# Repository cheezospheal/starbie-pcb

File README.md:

# Starbie
A custom-designed PCB for a portable, interactive pet keychain that reacts to different user actions and the environment.

I initially made it only because it was the beginner project for Half Life, but I've also always been a fan of these kinds of toys. It's not only relatively easy to make, but also teaches most of the fundamentals of PCB building, such as footprints, Silkscreen, and basic Arduino code. I'm more of a creative than technical person, but I felt that this was the perfect beginner project that enhanced both. I was already interested in exploring electronics, and, using some of my own skills and interests, I think my Starbie turned out great! :)

## Summary
The PCB was designed with **KiCad** and the code was made with **Arduino**. To open the PCB yourself, install both KiCad and Arduino, then import the respective files (see below).

|File|What's Inside?|
|---|---|
|starbie_pcb.kicad_pcb|contains the PCB layout, including the routing, footprints, and edge cuts
|starbie_pcb.kicad_pro|contains the project settings and configuration
|starbie_pcb.kicad_sch|contains the schematic and connections
|Starbie.ino|contains the code used to run the micrcontroller
|starbie_pcb_gerbers.zip|contains several gerber files
|bom.csv|bill of materials

## Features
* An OLED screen that displays a small Jolteon that you can interact with
* Pet actions, including sleeping, playing, petting, and jumping
* Button controls that allow the user to trigger animations
* Custom PCB shape of a star
* Customizable interactions in the Arduino code

## Schematic
To see the schematic, open up the kicad_sch file. In the schematic, there'll be some main parts:
* XIAO-ESP32-C3-SMD: The microcontroller of the project, interpreting and executing the code
* DHT11: A sensor for temperature and humidity for interactions with the pet
* R1 10k: A 10k Ohm resistor for the DHT11
* Conn_01x08_Pin and Conn_01x04_Pin: A connector pin that links each pin to its matching circuit trace
* SW_Push: A switch/button that will control actions for the pet

The way they are connected is either through wires or through net labels (which connect parts without having to draw long wires). 

## Routing & PCB Customization
After that, take a look at the routing by opening up the kicad_pcb file.

The red lines represent the copper traces on the front of the board, while the blue lines represent the copper traces on the black of the board. These copper lines allow the microcontroller to transmit and receive data to interpret, which will then be used for the pet. Furthermore, the red overlay on top of the PCB is the GND pour. Another thing you'll notice is the customization of the PCB, including the text, images, and shape of the PCB. The shape was made using the Edge Cuts layer. To edit it, draw your own lines or move the existing vertices. Just note that you'll have to edit the GND pour as well and refill it by pressing B. I also added an extra switch, which you can see in the bottom right corner of the star. To add images, use the image converter to turn the image into a bitmap, then into a footprint, and add it on as a footprint by pressing A. KiCad has a built-in text function, so you can use that as well. Also, make sure to put the layer for both images and text as F.Silkscreen!

For my images, I uploaded a sprite of Jolteon, an apple core, and some sparkles using the method above. Just make sure that, if you are using a sprite for a game, find a scaled-up version rather than the original sprites. I also added a keychain hole as a mounting hole. KiCad will scale-up the sprite into a blurry mess that looks nothing like the original sprite. I used Wingdings for my font because it looks more interesting than just a basic readable font. 

KiCad also has a 3D viewer so you can see what your PCB will probably eventually look like!

## Firmware Customization
After making the PCB, move on to the firmware in Arduino. The code was very easy to customize, so here's the things I did to change it up and make it my own. (to change it yourself, find the specific functions)

The pet comes with basic hearts, so I decided to replace it with a lightning bolt instead. I first drew it in Piskel (or use whatever sprite art app you have), and then just wrote the code to draw it by hand. The drawPixel function works as if you were drawing pixels relative to a certain point. So, if you wanted to draw a pixel 1 pixel left of the "anchor point", you would use x - 1. 

I also used the same logic to write some code for the sparkle trail, which I just replaced with a slightly bigger sparkle that I liked better.

The biggest part was designing the pet sprite, which I have as a Jolteon. Simply draw your creature in a 32x32 size, and upload it to an image2cpp converter. I find it best to draw your own sprite. Though Jolteon already exists and there are sprites of it, it's way more personal making your own! 

the sprite I made -> 

I also made the third switch that I added have a function by making it do the ATTACK animation when pressed.

## Bill of Materials
After completely designing the PCB and finishing your code, start planning for when you actually build your PCB by ordering the parts! I created a Bill of Materials (BOM), which lists the specific names, quantities, and prices for the parts of the PCB. Use the collection of gerber files, starbiepcb_gerbers.zip, when manufacturing the PCB. The BOM is both below and in bom.csv.

Part|Quantity|Price (USD)|Vendor|Link
|---|---|---|---|---|
XIAO ESP32C3|1|$10.11|Amazon|https://www.amazon.ca/MiiElAOD-High-Performance-Cost-Effective-1PCS-Kit/dp/B0GDG7YRGW/ref=asc_df_B0GDG7YRGW?mcid=c3c8863449923deb82a1a4779cbbab0e&tag=googleshopc0c-20&linkCode=df0&hvadid=803091086323&hvpos=&hvnetw=g&hvrand=8414720962410478217&hvpone=&hvptwo=&hvqmt=&hvdev=c&hvdvcmdl=&hvlocint=&hvlocphy=9000910&hvtargid=pla-2493221044780&hvocijid=8414720962410478217-B0GDG7YRGW-&hvexpln=0&gad_source=1&th=1
"OLED 0.96"" I2C display"|1|$3.50|Universal Solder|https://www.universal-solder.ca/product/oled-i2c-0-96-inch-128x64-pixel-ssd1306-sh1106-3-5v/
MPU6050 motion sensor|1|$3.69|Universal Solder|https://www.universal-solder.ca/product/invensense-mpu-6050-6-axis-gyro-accelerometer-module/
10k Resistor|1|$2.07|Sayal Electronics|https://secure.sayal.com/STORE4/prodetails.php?SKU=199179
DHT11 temperature sensor|1|$2.80|BC Electronics|https://bc-robotics.com/shop/dht11-temperature-humidity-sensor/?srsltid=AU7gw4ULU6YRGfsQBjuDnRTJuYX4SkghHcUgPcuIQJyEpNFTL2x4pbFyWcQ
MX Switches|1|$1.83|Amazon|https://www.amazon.ca/Generic-Mechanical-Replacement-Transparent-Experience/dp/B0GLHJQGD3/ref=sr_1_22?crid=1N8868XKKIUWJ&dib=eyJ2IjoiMSJ9.ZpmPzv0I6Ilteff9dFWN4NrcibU4l4RNK3l0ejiIi1fe5Z9izVKID2l5ML8P-Zh-qx9M7m6GS1BwTNYGjuMuoQUiomnBASgPFnM346gCD0M0Gr7ZHteRaXSSOxE6mx5UP36czPogMunnKkvJVZ0kVUY-rNlidTh7pt058naK8sQlQbCbPAhXv2xE_Occ2JLEH74Jlooi-ykvYvcHwkTBVsQRnQ73PgBn6NclhZN5sDXbEJwv9wQVq0LXx4d0aIY916GQEiCXIJ31wq70dm3ONwAdQlrSiuj9f6kdXsisOds.OqesYboksp47K2TkGj2qZPaHTt9My65icp_2Y1-FLL0&dib_tag=se&keywords=mx+key+switches&qid=1791756158&refinements=p_36%3A-1000&rnid=12035759011&sprefix=mx+key+switche%2Caps%2C159&sr=8-22&qty=1&psc=1&sbo=RZvfv%2F%2FHxDF%2BO5021pAnSA%3D%3D
MX Switch Keycaps|1|$6.01|Amazon|https://www.amazon.ca/Profile-Mechanical-Keyboard-Installation-Sublimated/dp/B0D1FSFG37/ref=sr_1_8?crid=32AZNZJ6HC2VP&dib=eyJ2IjoiMSJ9.M1aJJ4SDWbSbarTmmhVoX_OSvyKJGZH3Io6A3D3g2lkaNKds4tSyoKL3NsBRJJaVLYPcI-mSI8HIrpkp7DlXMo_uT3zxMyMb-PmTEmFrrMNIhKMtCo60_Th9nMHQylEY9pXecA4352OuV5zBExydxYPKX4vCqc6YtayF9UyR0gBekyN8QJgGQvW2s12Qtfzy2DyRWE1LPRzV42bWGfB3TmTe6BOtw39t2lB2afE4jnpcIO7WPwvNblqQl_bEikbem1rIs8m43OsXU2y3NiUu5CDMTB8qiWmHbwTFUvc8Lc8.UrV5txzs9T_ENm9jfr3SZ0UiVQLqVuGu6cEPNW6-8Yw&dib_tag=se&keywords=OEM%2BProfile%2BWhite%2BBlank%2BKeycaps%2BPBT%2BMaterial%2B1U%2BR4%2BKeycap%2Bfor%2BMX%2Bswitches%2BMechanical%2BKeyboard%2B(White%2C%2B20pcs)&qid=1791692286&sprefix=oem%2Bprofile%2Bwhite%2Bblank%2Bkeycaps%2Bpbt%2Bmaterial%2B1u%2Br4%2Bkeycap%2Bfor%2Bmx%2Bswitches%2Bmechanical%2Bkeyboard%2Bwhite%2C%2B20pcs%2B%2Caps%2C147&sr=8-8&th=1
PCB|1|$4.00|JLCPCB|https://cart.jlcpcb.com/quote?stencilLayer=2&stencilWidth=100&stencilLength=100&stencilCounts=5&plateType=1&spm=Jlcpcb.Homepage.1010
Shipping & Taxes|-|$39.11|-|-

## Extra Notes [Half-Life]
When reviewing the BOM, note that, for some vendors, I had specific promotions/coupons that helped reduce the shipping price. For example, there is a light-package promotion for BC Robotics that allow for free shipping during the fall. This is why my BOM fits under $30 in BOM.md even though the shipping is almost $40 in bom.csv. These promotions may not be applicable to everybody. Furthermore, the shipping and taxes are based on Ontario GST and HST, and it ships to an Ontario address. Therefore, prices may vary based on your location. I am also going to be buying some parts out of my own pocket (not with the grant), which have a price of $0.01 in the BOM.

The cart screenshots submitted on the Half-Life website are in CAD, not USD. The links also lead to Canadian websites that are in CAD. Each individual item in BOM.md was converted from CAD to USD. Because of this, there is a small rounding error due to the exchange rate. As a result, if you add up the cart totals together and convert to USD, it will be slightly off from the BOM, though I will be able to purchase the rest of the rounding if necessary. 

I had so much fun creating my Starbie and I can't wait to get into the other projects! ☆

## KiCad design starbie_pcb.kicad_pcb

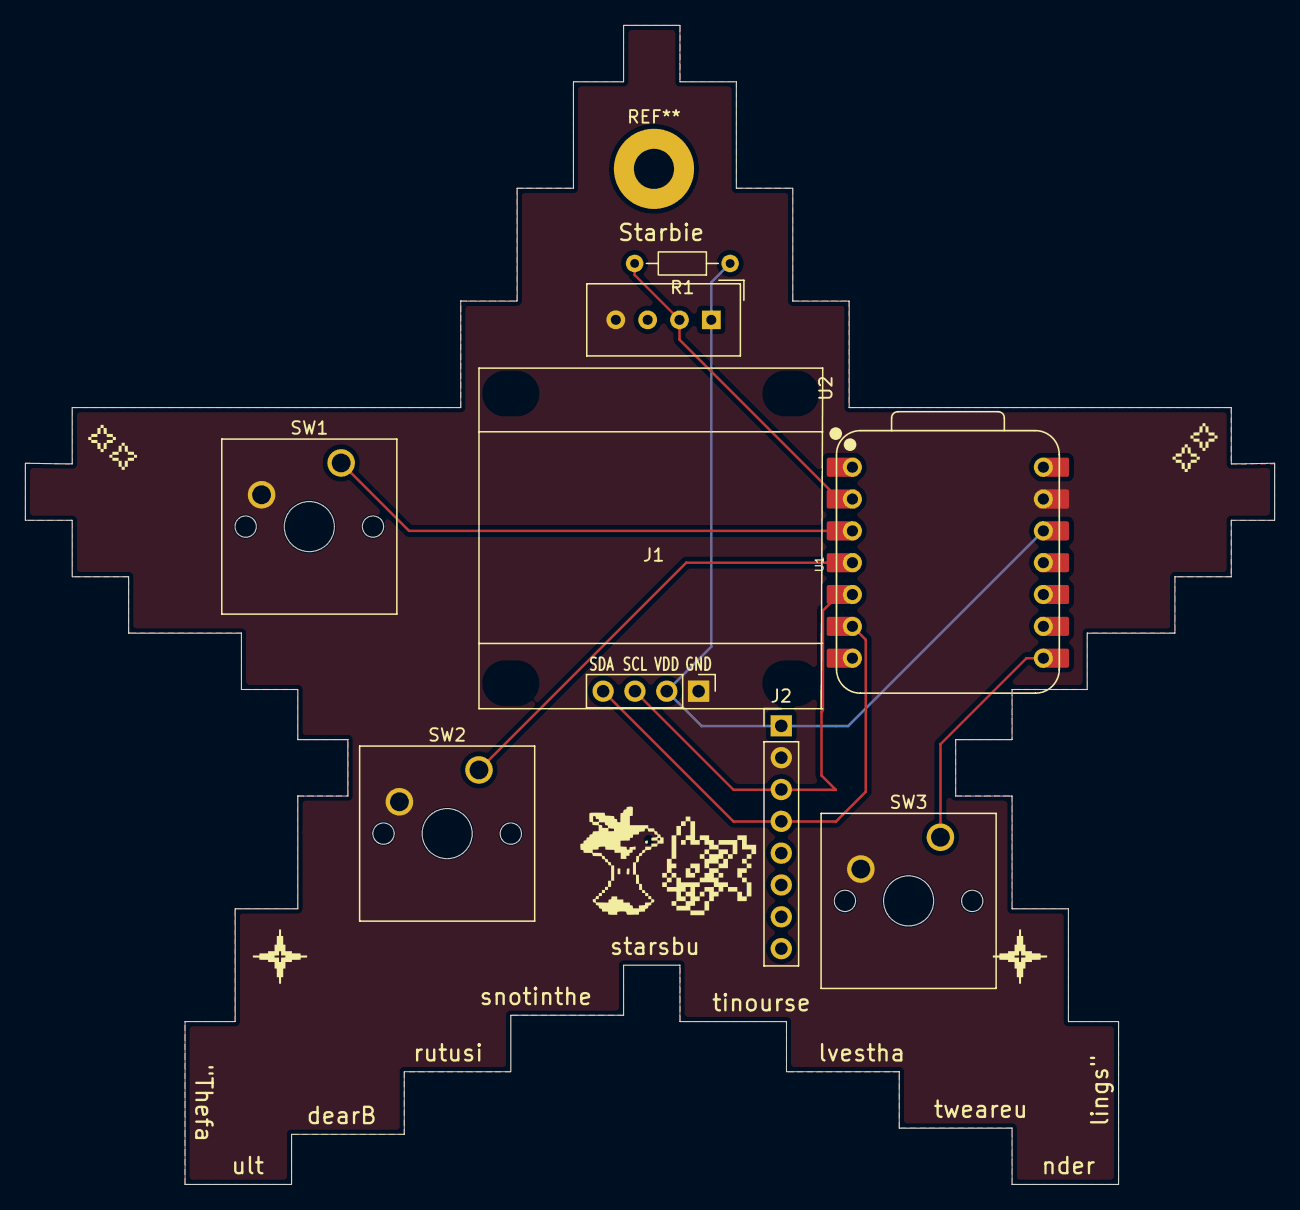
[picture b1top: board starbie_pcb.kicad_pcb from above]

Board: 2 copper layers, 99.7 x 92.5 mm, 8 parts (0 on the bottom side), 8 nets.

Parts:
J1: Conn_01x04_Pin; Display_128x64_096_I2C
J2: Conn_01x08_Pin; PinHeader_1x08_P2.54mm_Vertical
R1: 10k; R_Axial_DIN0204_L3.6mm_D1.6mm_P7.62mm_Horizontal
SW1, SW2, SW3: SW_Push; SW_Cherry_MX_1.00u_PCB
U1: XIAO-ESP32-C3-SMD; XIAO-ESP32-C6-DIP
U2: DHT11; Aosong_DHT11_5.5x12.0_P2.54mm

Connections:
+3.3V: J1.2, J2.1, R1.1, U1.12 (3V3_OUT), U2.1 (VDD)
/DHT11 DATA: R1.2, U1.2 (D1), U2.2 (DATA)
/GPIO2: SW1.1, U1.3 (D2)
/GPIO3: SW2.1, U1.4 (D3)
/GPIO7: SW3.1, U1.8 (D7)
/SCL: J1.3, J2.3, U1.5 (D4)
/SDA: J1.4, J2.4, U1.6 (D5)
GND: J1.1, J2.2, SW1.2, SW2.2, SW3.2, U1.13 (GND), U2.4 (GND)
